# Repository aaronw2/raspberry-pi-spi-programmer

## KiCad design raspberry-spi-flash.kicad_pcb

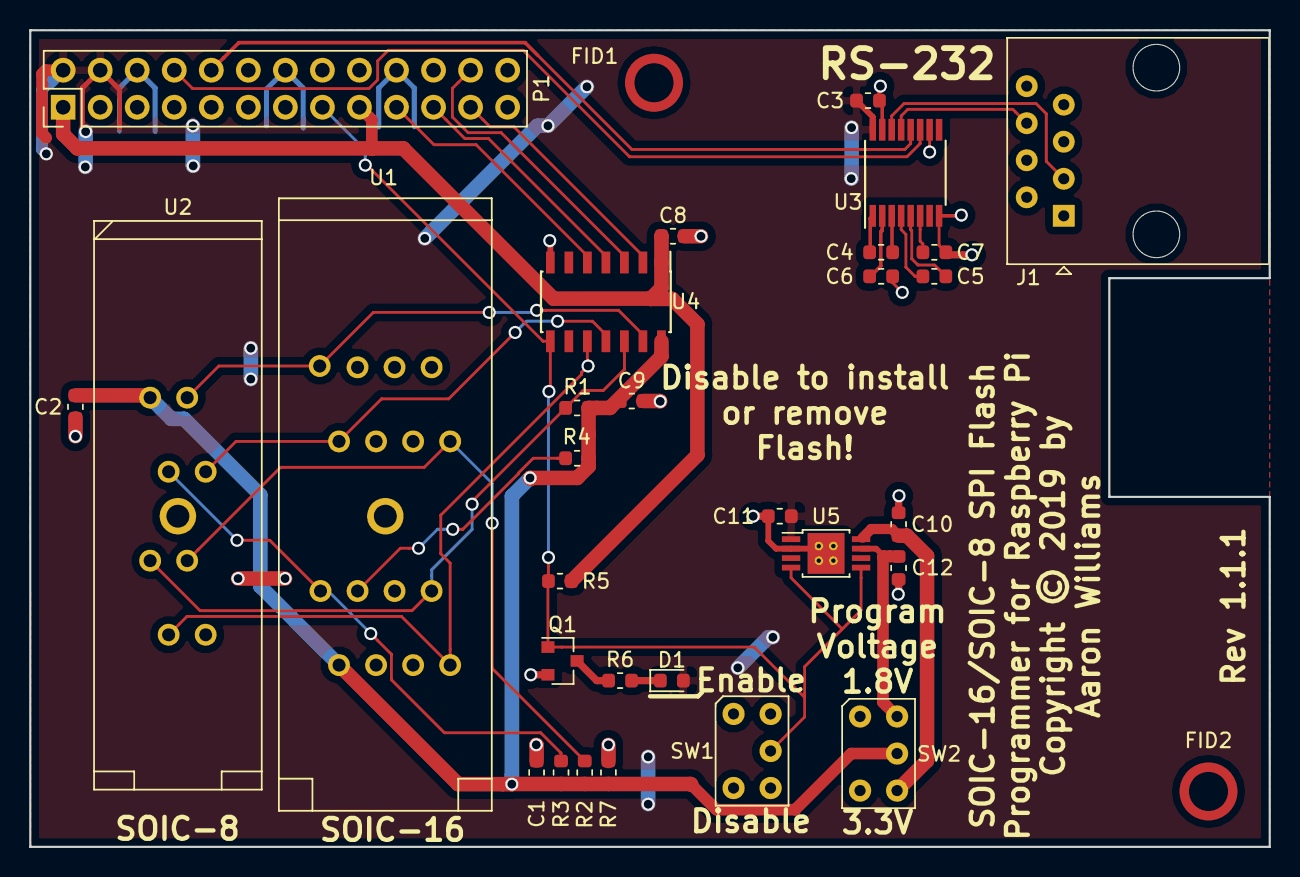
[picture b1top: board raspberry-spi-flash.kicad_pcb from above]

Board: 2 copper layers, 85.0 x 56.0 mm, 32 parts (0 on the bottom side), 30 nets.

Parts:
C1, C2, C3, C4, C5, C6, C7, C8, C9: 0.1uF; C_0603_1608Metric
C10, C11, C12: 4.7uF; C_0603_1608Metric
D1: LED; LED_0603_1608Metric
FID1, FID2: FIDUCIAL_1MM; Fiducial_Modern_CopperTop
J1: RJ45; RJ45_Amphenol_54602-x08_Horizontal
P1: CONN_13X2; PinHeader_2x13_P2.54mm_Vertical
Q1: BSS138; SOT-23
R1, R2, R3, R4, R5, R7: 4.75K; R_0603_1608Metric
R6: 560; R_0603_1608Metric
SW1, SW2: SW_SPDT; SW_STDP_CF-LD-1DC
U1: MX25L25735; 216-7224-55-1902
U2: AT25SF081-SSHD-X; 208-7391-55-1902
U3: MAX3232; TSSOP-16_4.4x5mm_P0.65mm
U4: TXB0104D; SOIC-14_3.9x8.7mm_P1.27mm
U5: MIC5355-SGYMME; MSOP-8-1EP_3x3mm_P0.65mm_EP2.54x2.8mm_ThermalVias

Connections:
+1V8: C12.1, SW2.1, U5.7
+3.3VP: C10.1, SW2.3, U5.8
+3V3: C8.1, P1.1, P1.17, R5.1, U4.1
+5V: C3.1, C11.1, D1.2, P1.2, P1.4, U3.16, U5.1
/FL_CS0: R1.2, U1.7, U2.1, U4.12
/GPIO8(CE0): P1.24, U4.3
/GPIO9(MISO): P1.21, U4.4
/GPIO10(MOSI): P1.19, U4.5
/GPIO11(SCLK): P1.23, U4.2
/GPIO22: P1.15, Q1.1, R5.2, SW1.2, U4.8, U5.4, U5.5
/MISO: U1.8, U2.2, U4.10
/MOSI: U1.15, U2.5, U4.11
/RXD: P1.10, U3.12
/SCLK: U1.16, U2.6, U4.13
/TXD: P1.8, U3.11
GND: C1.2, C2.2, C3.2, C6.2, C7.2, C8.2, C9.2, C10.2, C11.2, C12.2, J1.4, P1.6, P1.9, P1.14, P1.20, P1.25, Q1.2, R7.2, SW1.3, U1.10, U2.4, U3.8, U3.10, U3.15, U4.7, U5.2, U5.9
unnamed: C4.1, U3.1
unnamed: C4.2, U3.3
unnamed: C5.1, U3.4
unnamed: C5.2, U3.5
unnamed: C6.1, U3.2
unnamed: C7.1, U3.6
unnamed: D1.1, R6.1
unnamed: J1.3, U3.14
unnamed: J1.6, U3.13
unnamed: Q1.3, R6.2
unnamed: R2.2, U1.9, U2.3
unnamed: R3.2, U1.1, U2.7
unnamed: R4.2, U1.3
VPP: C1.1, C2.1, C9.1, R1.1, R2.1, R3.1, R4.1, R7.1, SW2.2, U1.2, U2.8, U4.14

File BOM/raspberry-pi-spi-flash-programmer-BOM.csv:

Refs,Value,Footprint,Quantity,MFR,MPN,SPR,SPN
U2,AT25SF081-SSHD-X,Aaron:208-7391-55-1902,1,3M,208-7391-55-1902,Digikey,3M5054-ND
U1,MX25L25735,Aaron:216-7224-55-1902,1,3M,216-7383-55-1902,Digikey,3M5078-ND
SW2;SW1,SW_SPDT,Aaron:SW_STDP_CF-LD-1DC,2,Nidec Copal Electronics,CF-LD-1DC-AW2W,Digikey,563-1944-ND
C1;C2;C4;C5;C3;C6;C7;C9;C8,0.1uF,Capacitor_SMD:C_0603_1608Metric,9,-,-,-,-
C10;C12;C11,4.7uF,Capacitor_SMD:C_0603_1608Metric,3,-,-,-,-
P1,CONN_13X2,Connector_PinHeader_2.54mm:PinHeader_2x13_P2.54mm_Vertical,1,-,-,-,-
J1,RJ45,Connector_RJ:RJ45_Amphenol_54602-x08_Horizontal,1,Amphenol,54602-908LF,Digikey,609-1046-ND
FID1;FID2,FIDUCIAL_1MM,Fiducial:Fiducial_Modern_CopperTop,2,-,-,-,-
D1,LED,LED_SMD:LED_0603_1608Metric,1,-,-,-,-
U5,MIC5355-SGYMME,Package_SO:MSOP-8-1EP_3x3mm_P0.65mm_EP2.54x2.8mm_ThermalVias,1,Microchip,MIC5355-SGYMME,Digikey,576-3882-5-ND
U4,TXB0104D,Package_SO:SOIC-14_3.9x8.7mm_P1.27mm,1,-,-,-,-
U3,MAX3232,Package_SO:TSSOP-16_4.4x5mm_P0.65mm,1,Texas Instruments,MAX3232ECPWR,Digikey,296-19263-1-ND
Q1,BSS138,Package_TO_SOT_SMD:SOT-23,1,ON Semiconductor,BSS138K,Digikey,BSS138KCT-ND
R4;R1;R3;R2;R5;R7,4.75K,Resistor_SMD:R_0603_1608Metric,6,-,-,-,-
R6,560,Resistor_SMD:R_0603_1608Metric,1,-,-,-,-

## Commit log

2019-01-13 Initial commit, revision 1.1
2019-01-13 Added missing README.md
2019-01-13 Added missing license
2019-01-16 Fixed typo
2019-01-26 Fixed solder mask clearance.
2019-01-26 Fixed footprint for soic-16 socket.
2019-01-30 Update README.md
    Obsoleting this.

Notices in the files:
raspberry-spi-flash.kicad_pcb:
Copyright © 2019 by
Aaron Williams
